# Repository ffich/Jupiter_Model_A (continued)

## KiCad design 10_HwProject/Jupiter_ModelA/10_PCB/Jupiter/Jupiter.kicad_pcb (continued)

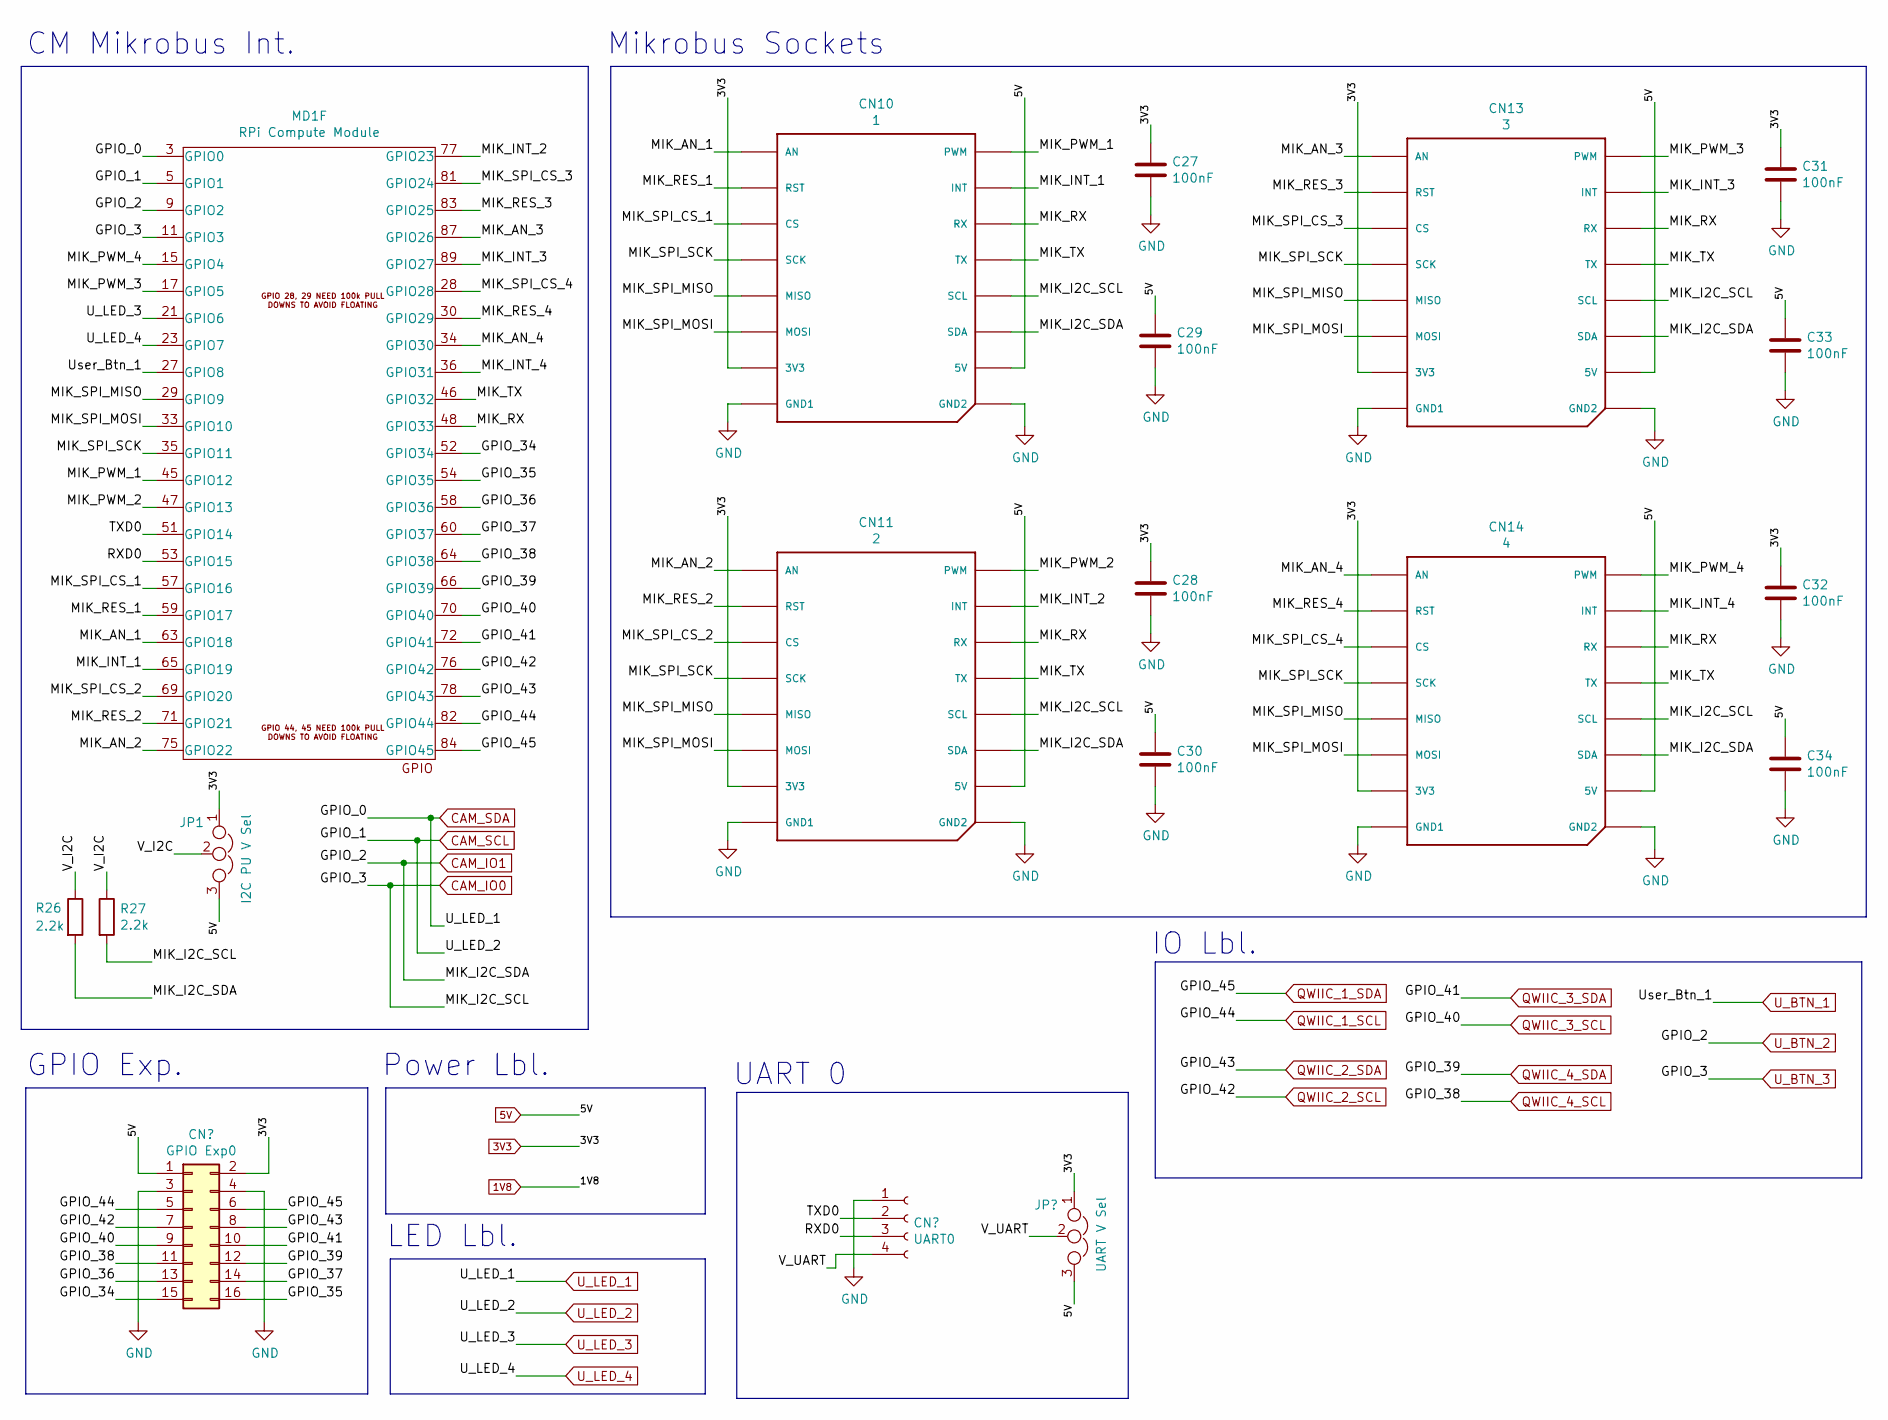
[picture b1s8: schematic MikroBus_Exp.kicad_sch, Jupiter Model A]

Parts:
C27, C28, C29, C30, C31, C32, C33, C34: 100nF; C_0805_2012Metric
CN9: GPIO Exp0; PinHeader_2x08_P2.54mm_Vertical
CN10: 1; MIKROBUS_HOST_CONN
CN11: 2; MIKROBUS_HOST_CONN
CN12: UART0; PinHeader_1x04_P2.54mm_Vertical
CN13: 3; MIKROBUS_HOST_CONN
CN14: 4; MIKROBUS_HOST_CONN
JP1: I2C PU V Sel; PinHeader_1x03_P2.54mm_Vertical
JP2: UART V Sel; PinHeader_1x03_P2.54mm_Vertical
MD1: RPi Compute Module; Conn_TE-DDR2-SODIMM-0.6-200P-doublesided
R26, R27: 2.2k; R_0603_1608Metric

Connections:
3V3: C27.1, C28.1, C31.1, C32.1, CN9.2, CN10.P7 (3V3), CN11.P7 (3V3), CN13.P7 (3V3), CN14.P7 (3V3), JP1.1, JP2.1; also elsewhere on the board
5V: C29.1, C30.1, C33.1, C34.1, CN9.1, CN10.P10 (5V), CN11.P10 (5V), CN13.P10 (5V), CN14.P10 (5V), JP1.3, JP2.3; also elsewhere on the board
/MikroBus_Exp/GPIO_34: CN9.15, MD1.52 (GPIO34)
/MikroBus_Exp/GPIO_35: CN9.16, MD1.54 (GPIO35)
/MikroBus_Exp/GPIO_36: CN9.13, MD1.58 (GPIO36)
/MikroBus_Exp/GPIO_37: CN9.14, MD1.60 (GPIO37)
/MikroBus_Exp/MIK_AN_1: CN10.P1 (AN), MD1.63 (GPIO18)
/MikroBus_Exp/MIK_AN_2: CN11.P1 (AN), MD1.75 (GPIO22)
/MikroBus_Exp/MIK_AN_3: CN13.P1 (AN), MD1.87 (GPIO26)
/MikroBus_Exp/MIK_AN_4: CN14.P1 (AN), MD1.34 (GPIO30)
/MikroBus_Exp/MIK_INT_1: CN10.P15 (INT), MD1.65 (GPIO19)
/MikroBus_Exp/MIK_INT_2: CN11.P15 (INT), MD1.77 (GPIO23)
/MikroBus_Exp/MIK_INT_3: CN13.P15 (INT), MD1.89 (GPIO27)
/MikroBus_Exp/MIK_INT_4: CN14.P15 (INT), MD1.36 (GPIO31)
/MikroBus_Exp/MIK_PWM_1: CN10.P16 (PWM), MD1.45 (GPIO12)
/MikroBus_Exp/MIK_PWM_2: CN11.P16 (PWM), MD1.47 (GPIO13)
/MikroBus_Exp/MIK_PWM_3: CN13.P16 (PWM), MD1.17 (GPIO5)
/MikroBus_Exp/MIK_PWM_4: CN14.P16 (PWM), MD1.15 (GPIO4)
/MikroBus_Exp/MIK_RES_1: CN10.P2 (RST), MD1.59 (GPIO17)
/MikroBus_Exp/MIK_RES_2: CN11.P2 (RST), MD1.71 (GPIO21)
/MikroBus_Exp/MIK_RES_3: CN13.P2 (RST), MD1.83 (GPIO25)
/MikroBus_Exp/MIK_RES_4: CN14.P2 (RST), MD1.30 (GPIO29)
/MikroBus_Exp/MIK_RX: CN10.P14 (RX), CN11.P14 (RX), CN13.P14 (RX), CN14.P14 (RX), MD1.48 (GPIO33)
/MikroBus_Exp/MIK_SPI_CS_1: CN10.P3 (CS), MD1.57 (GPIO16)
/MikroBus_Exp/MIK_SPI_CS_2: CN11.P3 (CS), MD1.69 (GPIO20)
/MikroBus_Exp/MIK_SPI_CS_3: CN13.P3 (CS), MD1.81 (GPIO24)
/MikroBus_Exp/MIK_SPI_CS_4: CN14.P3 (CS), MD1.28 (GPIO28)
/MikroBus_Exp/MIK_SPI_MISO: CN10.P5 (MISO), CN11.P5 (MISO), CN13.P5 (MISO), CN14.P5 (MISO), MD1.29 (GPIO9)
/MikroBus_Exp/MIK_SPI_MOSI: CN10.P6 (MOSI), CN11.P6 (MOSI), CN13.P6 (MOSI), CN14.P6 (MOSI), MD1.33 (GPIO10)
/MikroBus_Exp/MIK_SPI_SCK: CN10.P4 (SCK), CN11.P4 (SCK), CN13.P4 (SCK), CN14.P4 (SCK), MD1.35 (GPIO11)
/MikroBus_Exp/MIK_TX: CN10.P13 (TX), CN11.P13 (TX), CN13.P13 (TX), CN14.P13 (TX), MD1.46 (GPIO32)
/MikroBus_Exp/RXD0: CN12.3, MD1.53 (GPIO15)
/MikroBus_Exp/TXD0: CN12.2, MD1.51 (GPIO14)
/MikroBus_Exp/V_I2C: JP1.2, R26.1, R27.1
/MikroBus_Exp/V_UART: CN12.4, JP2.2
CAM_IO0: CN10.P12 (SCL), CN11.P12 (SCL), CN13.P12 (SCL), CN14.P12 (SCL), MD1.11 (GPIO3), R27.2; also elsewhere on the board
CAM_IO1: CN10.P11 (SDA), CN11.P11 (SDA), CN13.P11 (SDA), CN14.P11 (SDA), MD1.9 (GPIO2), R26.2; also elsewhere on the board
CAM_SCL: MD1.5 (GPIO1); also elsewhere on the board
CAM_SDA: MD1.3 (GPIO0); also elsewhere on the board
GND: C27.2, C28.2, C29.2, C30.2, C31.2, C32.2, C33.2, C34.2, CN9.3, CN9.4, CN10.P8 (GND1), CN10.P9 (GND2), CN11.P8 (GND1), CN11.P9 (GND2), CN12.1, CN13.P8 (GND1), CN13.P9 (GND2), CN14.P8 (GND1), CN14.P9 (GND2); also elsewhere on the board
QWIIC_1_SCL: CN9.5, MD1.82 (GPIO44); also elsewhere on the board
QWIIC_1_SDA: CN9.6, MD1.84 (GPIO45); also elsewhere on the board
QWIIC_2_SCL: CN9.7, MD1.76 (GPIO42); also elsewhere on the board
QWIIC_2_SDA: CN9.8, MD1.78 (GPIO43); also elsewhere on the board
QWIIC_3_SCL: CN9.9, MD1.70 (GPIO40); also elsewhere on the board
QWIIC_3_SDA: CN9.10, MD1.72 (GPIO41); also elsewhere on the board
QWIIC_4_SCL: CN9.11, MD1.64 (GPIO38); also elsewhere on the board
QWIIC_4_SDA: CN9.12, MD1.66 (GPIO39); also elsewhere on the board
U_BTN_1: MD1.27 (GPIO8); also elsewhere on the board
U_LED_3: MD1.21 (GPIO6); also elsewhere on the board
U_LED_4: MD1.23 (GPIO7); also elsewhere on the board

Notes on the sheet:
GPIO Exp.
IO Lbl.
CM Mikrobus Int.
UART 0
Mikrobus Sockets
Power Lbl.
LED Lbl.

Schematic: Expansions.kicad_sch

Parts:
CN15: QWIIC#1; JST_SH_SM04B-SRSS-TB_1x04-1MP_P1.00mm_Horizontal
CN16: QWIIC#2; JST_SH_SM04B-SRSS-TB_1x04-1MP_P1.00mm_Horizontal
CN17: GROVE#1; JST_PH_S4B-PH-SM4-TB_1x04-1MP_P2.00mm_Horizontal
CN18: GROVE#2; JST_PH_S4B-PH-SM4-TB_1x04-1MP_P2.00mm_Horizontal
LD4: U_LED_1; LED_0805_2012Metric
LD5: U_LED_2; LED_0805_2012Metric
LD6: U_LED_3; LED_0805_2012Metric
LD7: U_LED_4; LED_0805_2012Metric
R28, R29, R30, R31: 220; R_0603_1608Metric
R32, R33, R34, R35, R36, R37, R38, R39: 2.2k; R_0603_1608Metric
SW1: Reset; SW_SPST_B3U-1000P
SW2: User1; SW_SPST_B3U-1000P
SW3: User2; SW_SPST_B3U-1000P
SW4: User3; SW_SPST_B3U-1000P

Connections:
3V3: CN15.2, CN16.2, CN17.2, CN18.2, R32.1, R33.1, R34.1, R35.1, R36.1, R37.1, R38.1, R39.1; also elsewhere on the board
CAM_IO0: SW4.1; also elsewhere on the board
CAM_IO1: SW3.1; also elsewhere on the board
CAM_SCL: LD5.2 (A); also elsewhere on the board
CAM_SDA: LD4.2 (A); also elsewhere on the board
GND: CN15.1, CN16.1, CN17.1, CN18.1, R28.2, R29.2, R30.2, R31.2, SW1.2, SW2.2, SW3.2, SW4.2; also elsewhere on the board
unnamed: LD4.1 (K), R28.1
unnamed: LD5.1 (K), R29.1
unnamed: LD6.1 (K), R30.1
unnamed: LD7.1 (K), R31.1
QWIIC_1_SCL: CN15.4, R33.2; also elsewhere on the board
QWIIC_1_SDA: CN15.3, R32.2; also elsewhere on the board
QWIIC_2_SCL: CN16.4, R35.2; also elsewhere on the board
QWIIC_2_SDA: CN16.3, R34.2; also elsewhere on the board
QWIIC_3_SCL: CN17.4, R37.2; also elsewhere on the board
QWIIC_3_SDA: CN17.3, R36.2; also elsewhere on the board
QWIIC_4_SCL: CN18.4, R39.2; also elsewhere on the board
QWIIC_4_SDA: CN18.3, R38.2; also elsewhere on the board
RUN: SW1.1; also elsewhere on the board
U_BTN_1: SW2.1; also elsewhere on the board
U_LED_3: LD6.2 (A); also elsewhere on the board
U_LED_4: LD7.2 (A); also elsewhere on the board

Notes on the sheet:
GROVE Exp.
Power Lbl.
LEDs
QWIIC Exp.
Buttons

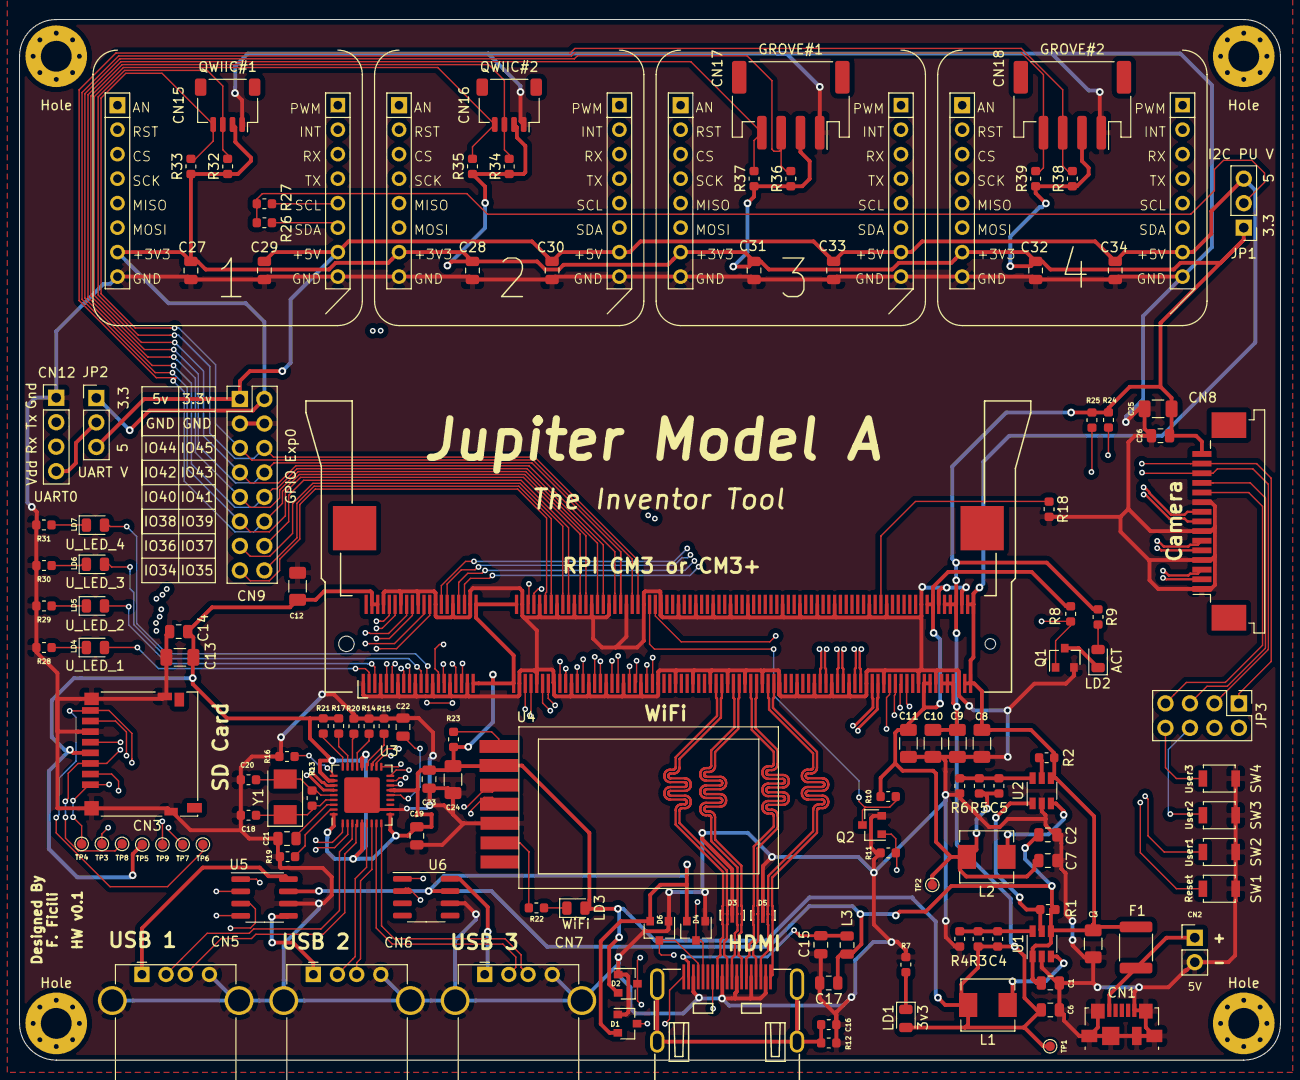
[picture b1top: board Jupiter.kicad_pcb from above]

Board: 4 copper layers, 130.8 x 108.0 mm, 138 parts (0 on the bottom side), 133 nets.

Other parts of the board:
Hole: MountingHole_3.2mm_M3_Pad_Via
Hole#2, Hole#3, Hole#4: MountingHole_3.2mm_M3_Pad_Via

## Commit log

2024-11-24 Update README.md
    Added various section to the document
2024-11-24 Update README.md
    Added dome photos
2024-11-24 Update README.md
    minor
2024-11-24 Create LICENSE
2024-11-24 minor on license
2024-11-24 Update README.md
    Added promo video
